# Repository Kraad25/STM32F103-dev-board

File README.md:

# STM32 Learning Project

A first PCB design project - an STM32F103C8T6 development board with USB, designed in KiCad while following Phil's Lab's PCB design course: <https://www.youtube.com/watch?v=aVUqaB0IMh4>

Guided by Phil's Lab's course - schematic and initial routing approach based on his walkthrough, with some layout and footprint adjustments made independently.

## Specs

- **MCU:** STM32F103C8T6
- **Power:** USB (5V), 3.3V via AMS1117-3.3 regulator
- **Interfaces:** USB (Micro-B), UART, SWD, I2C
- **Layers:** 2-layer, 1oz copper
- **Board size:** 32 x 32mm, 3mm corner radius
- **Status:** DRC-clean, manufacturing files generated (Gerbers, BOM, CPL)

## PCB Design

### Schematic

### PCB Layout

### 3D Renders

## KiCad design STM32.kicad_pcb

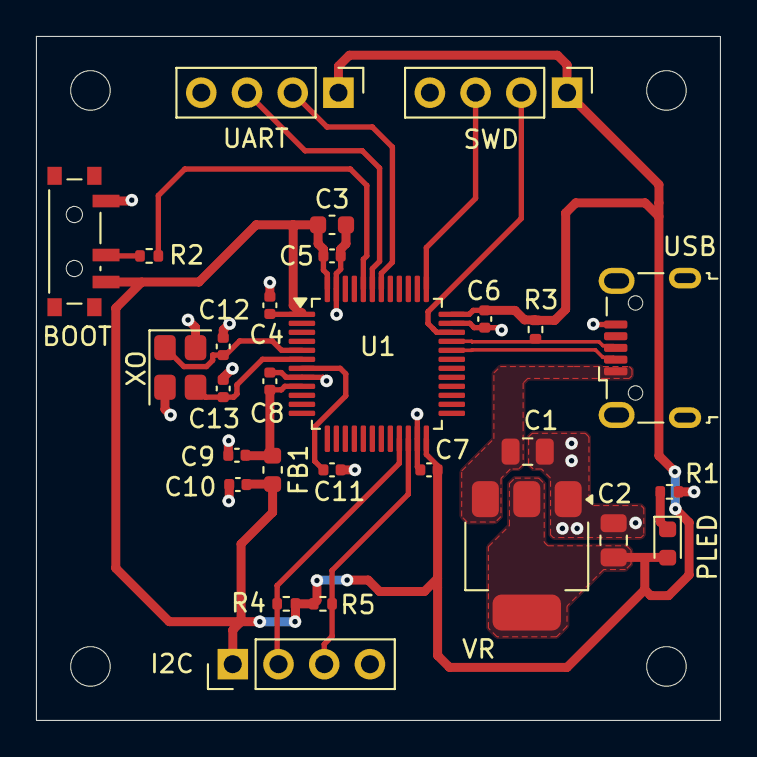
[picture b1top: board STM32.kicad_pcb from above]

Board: 2 copper layers, 38.0 x 38.0 mm, 32 parts (0 on the bottom side), 18 nets.

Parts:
BOOT: SW_SPDT; Boot_switch_custom
C1, C2: 22u; C_0805_2012Metric
C3: 10u; C_0603_1608Metric
C4, C5, C6, C7, C11: 100n; C_0402_1005Metric
C8: 10n; C_0402_1005Metric
C9, C10: 1u; C_0402_1005Metric
C12, C13: 10p; C_0402_1005Metric
FB1: 120R; L_0603_1608Metric
H1, H2, H3, H4: MountingHole; MountingHole_2.2mm_M2
I2C: Conn_01x04_Pin; PinHeader_1x04_P2.54mm_Vertical
PLED: RED; LED_0603_1608Metric
R1, R3, R4, R5: 1.5k; R_0402_1005Metric
R2: 10k; R_0402_1005Metric
SWD: Conn_01x04_Pin; PinHeader_1x04_P2.54mm_Vertical
U1: STM32F103C8T6; LQFP-48_7x7mm_P0.5mm
UART: Conn_01x04_Pin; PinHeader_1x04_P2.54mm_Vertical
USB: USB_B_Micro; USB_Micro-B_Wuerth_629105150521
VR: AMS1117-3.3; SOT-223-3_TabPin2
XO: 16MHz; Crystal_SMD_3225-4Pin_3.2x2.5mm

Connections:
+3.3V: BOOT.3 (C), C2.1, C3.1, C4.1, C5.1, C6.1, C7.1, C10.1, FB1.2, I2C.1, PLED.2 (A), R3.1, R4.1, R5.1, SWD.1, U1.1 (VBAT), U1.24 (VDD), U1.36 (VDD), U1.48 (VDD), UART.1, VR.2 (VO)
+3.3VA: C8.1, C9.1, FB1.1, U1.9 (VDDA)
/BOOT0: R2.2, U1.44 (BOOT0)
/HSE_IN: C12.1, U1.5 (PD0), XO.1
/HSE_OUT: C13.1, U1.6 (PD1), XO.3
/I2C2_SCL: I2C.2, R4.2, U1.21 (PB10)
/I2C2_SDA: I2C.3, R5.2, U1.22 (PB11)
/NRST: C11.1, U1.7 (NRST)
/Power_Led_C: PLED.1 (K), R1.1
/SWCLK: SWD.3, U1.37 (PA14)
/SWDIO: SWD.2, U1.34 (PA13)
/SW_BOOT0: BOOT.2 (B), R2.1
/USART1_RX: U1.43 (PB7), UART.3
/USART1_TX: U1.42 (PB6), UART.2
/USB_D+: R3.2, U1.33 (PA12), USB.3 (D+)
/USB_D-: U1.32 (PA11), USB.2 (D-)
GND: BOOT.1 (A), C1.2, C2.2, C3.2, C4.2, C5.2, C6.2, C7.2, C8.2, C9.2, C10.2, C11.2, C12.2, C13.2, I2C.4, R1.2, SWD.4, U1.8 (VSSA), U1.23 (VSS), U1.35 (VSS), U1.47 (VSS), UART.4, USB.5 (GND), VR.1 (GND), XO.2 (G), XO.4 (G)
VBUS: C1.1, USB.1 (VBUS), VR.3 (VI)
